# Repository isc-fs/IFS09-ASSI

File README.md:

# IFS09-ASSI

Hardware design (KiCad schematic and PCB layout) for the **Autonomous System Status Indicator (ASSI)** board of the **IFS09**, developed for the **ISC Formula Student Racing Team** (Season 2026/2027).

[-green.svg)]()

---

## Getting started

1. Create a GitHub account if you don't have one yet.
2. Download and install [GitHub Desktop](https://desktop.github.com/) (beginner) or [Git CLI](https://git-scm.com/book/en/v2/Getting-Started-Installing-Git) (advanced).

   - If this is your first time using GitHub Desktop, make sure to read the [User Manual](https://help.github.com/desktop/guides/).
   - If this is your first time using Git, start with a tutorial. There are many available online:
     - [Git Tutorial](https://git-scm.com/docs/gittutorial)
     - [Atlassian Git Tutorial](https://www.atlassian.com/git/tutorials/)
   - Keep a copy of [GitHub's Git Cheat Sheet](https://services.github.com/kit/downloads/github-git-cheat-sheet.pdf) handy as a reference.

3. Clone this repository to your machine:
   - SSH: `git@github.com:isc-fs/IFS09-ASSI.git`
   - HTTPS: `https://github.com/isc-fs/IFS09-ASSI.git`

4. To open the design, install [KiCad 10](https://www.kicad.org/download/) and set up the team library [IFS-KicadLib](https://github.com/isc-fs/IFS-KicadLib) (`ISC_KICAD_LIB` path variable), then open `hardware/ASSI/ASSI.kicad_pro`.

---

## How we work with this repository

### Main branches

The repository has two permanent branches:

**`main`** is the production branch. It contains only validated code that can be flashed onto the car. Never work directly on it.

**`dev`** is the development branch. It is the integration point where everyone's work comes together. Never work directly on it either — all changes arrive through a feature branch.

```
main  ──────────────────●──────────────────────●──▶  (validated releases only)
                        ↑                      ↑
dev   ──────●───●───●───●───●───●───●───●───●──●──▶  (continuous integration)
            ↑   ↑       ↑   ↑   ↑       ↑   ↑
          feat/1 fix/1 feat/2 fix/2   feat/3 fix/3
```

### Feature branches

All work — whether a new feature or a bug fix — is done on a **feature branch** created from `dev`. When the work is ready, a Pull Request is opened toward `dev`, reviewed, merged, and the branch is deleted.

There are two branch types, each with its own independent numeric counter:

```
feat/<n>   →  new functionality  (feat/1, feat/2, feat/3 ...)
fix/<n>    →  bug fix            (fix/1,  fix/2,  fix/3  ...)
```

The `feat` and `fix` counters are independent: `feat/2` and `fix/2` can exist at the same time with no conflict.

### Tracking branch history

Feature branches are deleted after merging to keep the repository clean. The history of each branch is preserved in **GitHub Issues**.

Every branch has one associated issue. The issue carries a **label** (`feat` or `fix`) and its title includes the branch number, for example: `[feat/3] Add CAN broadcast for mission state`. When the branch is merged and deleted, the issue is closed — becoming a permanent record of all the work done.

To see which branches are currently active: filter issues by label and status `open`.
To browse the full history: filter by label and status `closed`.
The number for the next branch of each type is the last closed issue of that type plus one.

> Example: if the last closed issue with label `feat` is `[feat/4] ...`, the next feature branch will be `feat/5`.

---

## Automation

The repository includes a GitHub Actions workflow that manages tracking issues automatically. No setup is required — it works for every developer as soon as they create a branch.

### Automatic issue creation

When a `feat/*` or `fix/*` branch is pushed to GitHub, the workflow automatically opens an issue with:

- The corresponding `[feat/N]` or `[fix/N]` title
- The correct label (`feat` or `fix`)
- A template with sections for describing the work and adding notes
- The name of the developer who created the branch

### Wrong number warning

If the branch number is not the next expected one (either too low or too high), the issue will display a warning indicating the correct number and asking the developer to delete and recreate the branch with the right name.

### Auto-fill description from first commit

When the developer makes their first commit and pushes it, the workflow automatically updates the *"What does this branch do?"* section of the issue with that commit message.

- If the developer manually edits the issue before pushing their first commit, the workflow will not overwrite the description.
- The description is only updated once — subsequent commits do not modify the issue.

---

## Step-by-step workflow

### 1. Create the branch

```bash
# Make sure you are on an up-to-date dev
git checkout dev
git pull origin dev

# Create your branch using the next available number for its type
# (last closed issue of that type + 1)
git checkout -b feat/5    # or fix/3, depending on that type's counter
```

> To find the right number: go to **Issues → filter by label `feat` or `fix` → sort by newest** and read the last number.

### 2. Push the branch

```bash
git push origin feat/5
```

The tracking issue will be opened automatically on GitHub within seconds.

### 3. Work and commit

```bash
# Make your changes and commit with a clear, descriptive message
git add .
git commit -m "short description of what this commit does"

# Push the changes
git push origin feat/5
```

The message of your **first commit** will be used to automatically fill in the issue description.

### 4. Open a Pull Request

When the work is ready, open a Pull Request on GitHub from your branch toward `dev`. In the PR description write `Closes #<issue-number>` so the issue closes automatically when the PR is merged.

Before requesting a review, check that:
- KiCad ERC and DRC report no errors
- The schematic PDF and the images in `docs/images/` match the design
- You have tested the change on the bench if applicable
- The PR targets `dev`, not `main`

### 5. Review and merge

Another team member will review the PR. Once approved, it is merged into `dev` and the branch is deleted. The issue will be closed as a permanent record.

### 6. Merging into main

When `dev` holds a set of validated changes that are ready for the car, a responsible team member opens a Pull Request from `dev` into `main`. This only happens after full firmware validation (HIL/bench).

---

## 1. Project overview

The ASSI shows the state of the Autonomous System to people around the car, as required by the Formula Student rules:

| AS state | ASSI |
| :--- | :--- |
| AS Off | Off |
| AS Ready | Yellow, continuous |
| AS Driving | Yellow, flashing |
| AS Emergency | Blue, flashing |
| AS Finished | Blue, continuous |

This board is a **passive LED board**: it has no microcontroller or logic. It lights yellow or blue depending on which of its two 24 V inputs is powered, so the colour and the flashing are decided by whatever drives those two lines.

```
            +--------------------- ASSI board ---------------------+
 IN1        |                                                      |        OUT1
 24V_YW ----+--> D2 --+--> R + G channels --> 3 rows x 5 LEDs --+  +---- 24V_YW
 24V_BL ----+--> D1 --+--> B channel -------> 3 rows x 5 LEDs --+  +---- 24V_BL
 GND -------+---------------------------------------------------+--+---- GND
            +------------------------------------------------------+
```

`IN1` and `OUT1` are wired pin to pin, so several ASSI boards can be daisy-chained from one harness branch.

### Mounting configuration

* Each ASSI is made of **two boards (A and B)** mounted next to each other, touching along the long edge, with the same orientation so the LED columns line up.
* The harness connects to `IN1` of board A, and board B connects to `OUT1` of board A (daisy chain). `OUT1` of board B is left unconnected.
* Board A carries the current of both boards: up to ~370 mA on `24V_BL` in blue mode.
* The car has three ASSIs (two sides and rear), so **6 boards** per car. A single board at the rear is being considered (5 boards per car).

---

## 2. Rules compliance (FS Rules 2026 v1.1)

| Rule | Requirement | This design |
| :--- | :--- | :--- |
| T 14.9.1 | Yellow/blue states as in the table above. "AS Driving" and "AS Emergency" flash at 2–5 Hz with 50 % duty cycle. | The board only lights the colour. The flashing frequency and duty cycle must be generated by the controller that drives `24V_YW` / `24V_BL`. |
| T 14.9.2 | Three ASSIs: one on each side behind the driver's compartment and one at the rear on the centreline. | Three ASSIs of two boards each (6 boards per car). |
| T 11.9.5 | Safe state of the ASSI signal is "AS Off". | With no supply the board is off. |
| T 11.10.1 | Black background. | The PCB solder mask is green: the enclosure must give a black background around the LEDs, or the board must be ordered with black solder mask. |
| T 11.10.1 | Minimum illuminated surface of 15 cm² with even luminous intensity. | Two boards: ≈ 40 cm² between LED centres (55.7 mm × ~72 mm). If the rear ASSI uses a single board, it has only ≈ 14.8 cm² between LED centres (≈ 20 cm² including the LED bodies), which is borderline, so that ASSI needs a diffuser or window of at least 15 cm² (see #16). |
| T 11.10.1 | LEDs without diffuser no more than 20 mm apart. | Within a board the LED pitch is 14 mm horizontally and 13 mm vertically. Between boards A and B the vertical distance is 18.7–19.2 mm, so it only stays below 20 mm if the boards touch and the LED columns are aligned. |
| T 11.10.1 | Clearly visible in very bright sunlight. | To be checked on the first boards (see #9). |

---

## 3. Schematic

<p align="center">
  
  <br>
  <sub><em>Click on the preview to open the vector PDF (<a href="Schematics-1.0.pdf">Schematics-1.0.pdf</a>)</em></sub>
</p>

### 3.1 Supply inputs

* **`24V_YW`** feeds the red and green LED channels together through diode `D2` (red + green = yellow).
* **`24V_BL`** feeds the blue LED channel through diode `D1`.
* `D1` and `D2` are Nexperia PMEG4010CEH Schottky diodes (1 A, 40 V, SOD-123F). They block reverse polarity on each input.
* `C4` (yellow rail) and `C3` (blue rail) are 100 nF 0805 capacitors to GND after each diode.

### 3.2 LED strings

* 15 × Cree **CLQ6B** RGBW LEDs (`LED1`–`LED15`), arranged as **3 rows of 5 LEDs in series**.
* Each row has its own 1206 series resistors per colour channel (`R1`–`R18`):
  * Red: 2 × 300 Ω in series (`R1`+`R2`, `R7`+`R9`, `R13`+`R15`)
  * Green: 1 × 1 kΩ (`R3`, `R10`, `R16`)
  * Blue: 3 × 47 Ω in series (`R4`+`R5`+`R6`, `R8`+`R11`+`R12`, `R14`+`R17`+`R18`)
* The white die of the CLQ6B is not used (see #17).

### 3.3 Currents and resistor power

String current: `I = (24 V − V_D − 5 × V_F) / R_string`, with V_D ≈ 0.4 V for the Schottky diode.

| Channel | V_F per LED (est.) | R_string | Current per string | Power per resistor (I²·R) |
| :--- | :---: | :---: | :---: | :---: |
| Red | 1.84 V | 600 Ω (2 × 300 Ω) | ~24 mA | ~173 mW |
| Green | 2.4 V | 1 kΩ | ~11.6 mA | ~135 mW |
| Blue | 3.0 V | 141 Ω (3 × 47 Ω) | ~61 mA | ~175 mW |

* Input current: ~183 mA on `24V_BL` (D1) and ~107 mA on `24V_YW` (D2), well below the 1 A rating of the PMEG4010CEH.
* Board dissipation: ~4.4 W in blue mode and ~2.6 W in yellow mode.
* V_F values are estimates. The currents must be confirmed on the first boards (see #6).

**Resistor rating check.** The resistors are Panasonic ERJ-P08 anti-surge thick film, 1206, **0.66 W**, ±1 %. Per the Panasonic datasheet, the rating is 100 % up to 70 °C ambient and derates linearly to 0 at 155 °C. Design rule: power ≤ 60 % of the derated rating.

| Board temperature | Derated rating | 60 % limit | Worst resistor (blue, 175 mW) |
| :---: | :---: | :---: | :---: |
| ≤ 70 °C | 0.66 W | 396 mW | 27 % of rating |
| 85 °C | 0.54 W | 326 mW | 32 % of rating |
| 100 °C | 0.43 W | 256 mW | 41 % of rating |

The 60 % rule is met for every resistor up to a board temperature of about 117 °C.

### 3.4 Connectors

`IN1` and `OUT1` are Molex Micro-Fit 3.0, 3 circuits, right-angle (43650-0300), with the same pinout:

| Pin | Net | Description |
| :---: | :--- | :--- |
| 1 | `GND` | Ground |
| 2 | `24V_YW` | 24 V supply for yellow |
| 3 | `24V_BL` | 24 V supply for blue |

The connectors overhang the board edge on purpose (see #13).

---

## 4. PCB layout

| Parameter | Value |
| :--- | :--- |
| Board size | 110 mm × 45 mm |
| Layers | 2, GND pour on both layers |
| Thickness | 1.6 mm |
| Track widths | 0.8 mm `Power` net class (`24V_YW`, `24V_BL`, `/G`, `/B`, `GND`), 0.5 mm `LED` net class (LED strings), 0.2 mm elsewhere |
| Vias | 27 × 0.6/0.3 mm, 15 of them GND stitching vias between both layers |
| Mounting holes | 4 × M3 (3.2 mm, non-plated, not connected to GND), with an 8 mm copper keep-out on both layers so the screw head and washer do not sit on copper |
| Other non-plated holes | 2 × 3.05 mm: locating pegs of the Micro-Fit connectors |
| Components | 37 SMD + 2 through-hole connectors, all on the top side |

---

## 5. Bill of materials

| Reference | Qty | Part | Manufacturer | MPN | Footprint |
| :--- | :---: | :--- | :--- | :--- | :--- |
| `LED1`–`LED15` | 15 | RGBW LED | CreeLED | CLQ6B-TKW-S1L1R1H1TBB7935BB3 | `ISC_modulos_pcb:SMT_B7935BB3_WFS` |
| `R1`, `R2`, `R7`, `R9`, `R13`, `R15` | 6 | Resistor, 300 Ω, 1 %, 0.66 W | Panasonic | ERJ-P08F3000V | `Resistor_SMD:R_1206_3216Metric_Pad1.30x1.75mm_HandSolder` |
| `R3`, `R10`, `R16` | 3 | Resistor, 1 kΩ, 1 %, 0.66 W | Panasonic | ERJ-P08F1001V | `Resistor_SMD:R_1206_3216Metric_Pad1.30x1.75mm_HandSolder` |
| `R4`–`R6`, `R8`, `R11`, `R12`, `R14`, `R17`, `R18` | 9 | Resistor, 47 Ω, 1 %, 0.66 W | Panasonic | ERJ-P08F47R0V | `Resistor_SMD:R_1206_3216Metric_Pad1.30x1.75mm_HandSolder` |
| `C3`, `C4` | 2 | Capacitor, 100 nF, 50 V, X7R | Samsung Electro-Mechanics | CL21B104KBCNNNC | `Capacitor_SMD:C_0805_2012Metric` |
| `D1`, `D2` | 2 | Schottky diode, 1 A, 40 V | Nexperia | PMEG4010CEH | `Diode_SMD:D_SOD-123F` |
| `IN1`, `OUT1` | 2 | Micro-Fit 3.0 header, 3P, right-angle | Molex | 43650-0300 | `ISC_conectores:CONN_SD-43650-001_03_MOL` |

The same list is exported as [`bom.csv`](hardware/ASSI/production/bom.csv), and the component positions as [`positions.csv`](hardware/ASSI/production/positions.csv).

---

## 6. Open points

| Issue | Status |
| :--- | :--- |
| #6 Thermal | Copper improvements done. The 30-minute bench test in blue mode is pending until boards are built. |
| #9 Yellow colour | To be checked in daylight on the first boards. |
| #10 TVS on the inputs | Low priority, not decided yet. |
| #14 3D models | To be added in IFS-KicadLib. |
| #15 Fiducials | Depends on how the board will be assembled. |
| #16 LED coverage of the board | With two boards per ASSI the illuminated surface is ≈ 40 cm². Still to be decided with the enclosure design, especially if the rear ASSI uses a single board (see T 11.10.1 above). |

---

## 7. Repository structure

```
hardware/ASSI/             KiCad project (schematic and PCB layout)
hardware/ASSI/production/  Fabrication output:
                             ASSI.zip       Gerber + drill package
                             netlist.ipc    IPC-D-356 netlist
                             bom.csv        Bill of materials with manufacturer and MPN
                             positions.csv  Component placement (pick and place)
Schematics-1.0.pdf         Schematic exported to PDF
docs/images/               Images used in this README
```

The CLQ6B symbol and footprint, the connector footprint and the ISC logo come from [IFS-KicadLib](https://github.com/isc-fs/IFS-KicadLib). The resistor, capacitor and diode footprints come from the standard KiCad libraries.

---

*ISC Racing Team — IFS09 Driverless*

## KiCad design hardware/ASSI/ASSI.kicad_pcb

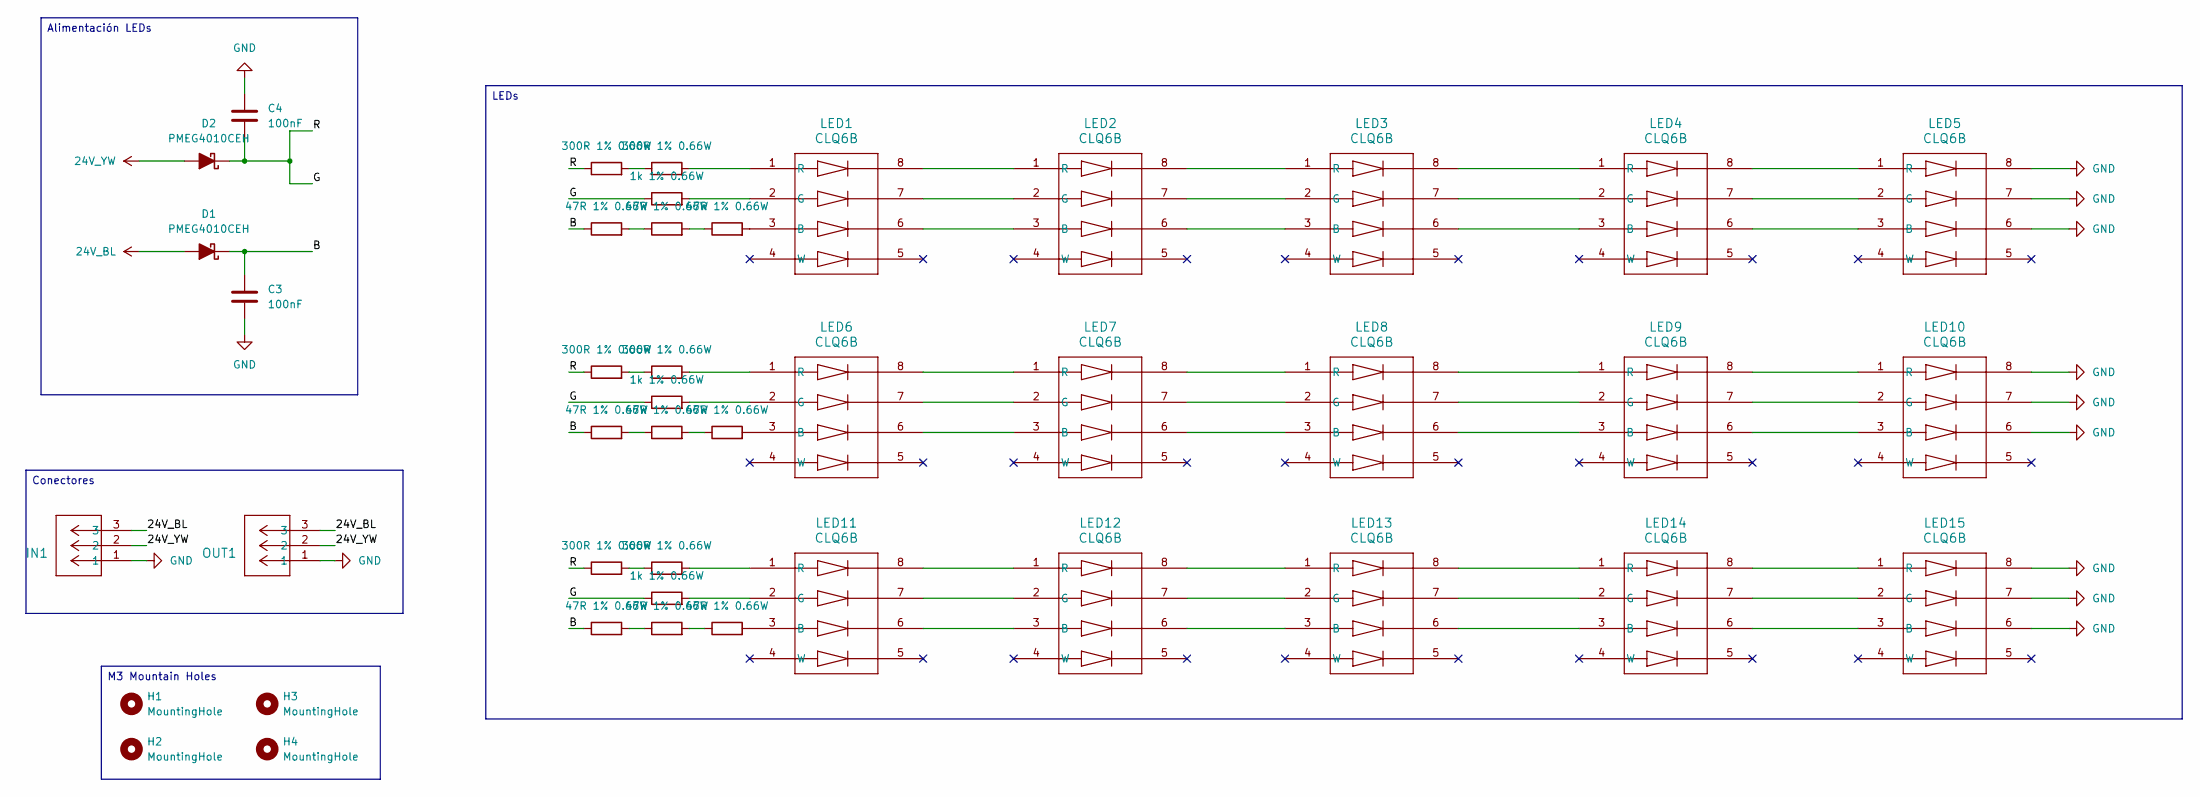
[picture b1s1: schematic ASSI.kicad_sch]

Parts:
C3, C4: 100nF; C_0805_2012Metric; MPN CL21B104KBCNNNC
D1, D2: PMEG4010CEH; D_SOD-123F; MPN PMEG4010CEH
H1, H2, H3, H4: MountingHole; MountingHole_3.2mm_M3
IN1: 436500300; CONN_SD-43650-001_03_MOL; MPN 43650-0300
LED1, LED2, LED3, LED4, LED5, LED6, LED7, LED8, LED9, LED10, LED11, LED12, LED13, LED14, LED15: CLQ6B; SMT_B7935BB3_WFS; MPN CLQ6B-TKW-S1L1R1H1TBB7935BB3
OUT1: 436500300; CONN_SD-43650-001_03_MOL; MPN 43650-0300
R1, R2, R7, R9, R13, R15: 300R 1% 0.66W; R_1206_3216Metric_Pad1.30x1.75mm_HandSolder; MPN ERJ-P08F3000V
R3, R10, R16: 1k 1% 0.66W; R_1206_3216Metric_Pad1.30x1.75mm_HandSolder; MPN ERJ-P08F1001V
R4, R5, R6, R8, R11, R12, R14, R17, R18: 47R 1% 0.66W; R_1206_3216Metric_Pad1.30x1.75mm_HandSolder; MPN ERJ-P08F47R0V

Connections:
24V_BL: D1.2 (A), IN1.3, OUT1.3
24V_YW: D2.2 (A), IN1.2, OUT1.2
/B: C3.1, D1.1 (K), R6.1, R8.1, R14.1
/G: C4.2, D2.1 (K), R2.1, R3.1, R7.1, R10.1, R13.1, R16.1
GND: C3.2, C4.1, IN1.1, LED5.6, LED5.7, LED5.8, LED10.6, LED10.7, LED10.8, LED15.6, LED15.7, LED15.8, OUT1.1
unnamed: LED1.3 (B), R4.2
unnamed: LED1.2 (G), R3.2
unnamed: LED1.1 (R), R1.2
unnamed: LED1.6, LED2.3 (B)
unnamed: LED1.7, LED2.2 (G)
unnamed: LED1.8, LED2.1 (R)
unnamed: LED2.6, LED3.3 (B)
unnamed: LED2.7, LED3.2 (G)
unnamed: LED2.8, LED3.1 (R)
unnamed: LED3.6, LED4.3 (B)
unnamed: LED3.7, LED4.2 (G)
unnamed: LED3.8, LED4.1 (R)
unnamed: LED4.6, LED5.3 (B)
unnamed: LED4.7, LED5.2 (G)
unnamed: LED4.8, LED5.1 (R)
unnamed: LED6.3 (B), R12.2
unnamed: LED6.2 (G), R10.2
unnamed: LED6.1 (R), R9.2
unnamed: LED6.6, LED7.3 (B)
unnamed: LED6.7, LED7.2 (G)
unnamed: LED6.8, LED7.1 (R)
unnamed: LED7.6, LED8.3 (B)
unnamed: LED7.7, LED8.2 (G)
unnamed: LED7.8, LED8.1 (R)
unnamed: LED8.6, LED9.3 (B)
unnamed: LED8.7, LED9.2 (G)
unnamed: LED8.8, LED9.1 (R)
unnamed: LED9.6, LED10.3 (B)
unnamed: LED9.7, LED10.2 (G)
unnamed: LED9.8, LED10.1 (R)
unnamed: LED11.3 (B), R18.2
unnamed: LED11.2 (G), R16.2
unnamed: LED11.1 (R), R15.2
unnamed: LED11.6, LED12.3 (B)
unnamed: LED11.7, LED12.2 (G)
unnamed: LED11.8, LED12.1 (R)
unnamed: LED12.6, LED13.3 (B)
unnamed: LED12.7, LED13.2 (G)
unnamed: LED12.8, LED13.1 (R)
unnamed: LED13.6, LED14.3 (B)
unnamed: LED13.7, LED14.2 (G)
unnamed: LED13.8, LED14.1 (R)
unnamed: LED14.6, LED15.3 (B)
unnamed: LED14.7, LED15.2 (G)
unnamed: LED14.8, LED15.1 (R)
unnamed: R1.1, R2.2
unnamed: R4.1, R5.2
unnamed: R5.1, R6.2
unnamed: R7.2, R9.1
unnamed: R8.2, R11.1
unnamed: R11.2, R12.1
unnamed: R13.2, R15.1
unnamed: R14.2, R17.1
unnamed: R17.2, R18.1

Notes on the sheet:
Conectores
M3 Mountain Holes
LEDs
Alimentación LEDs

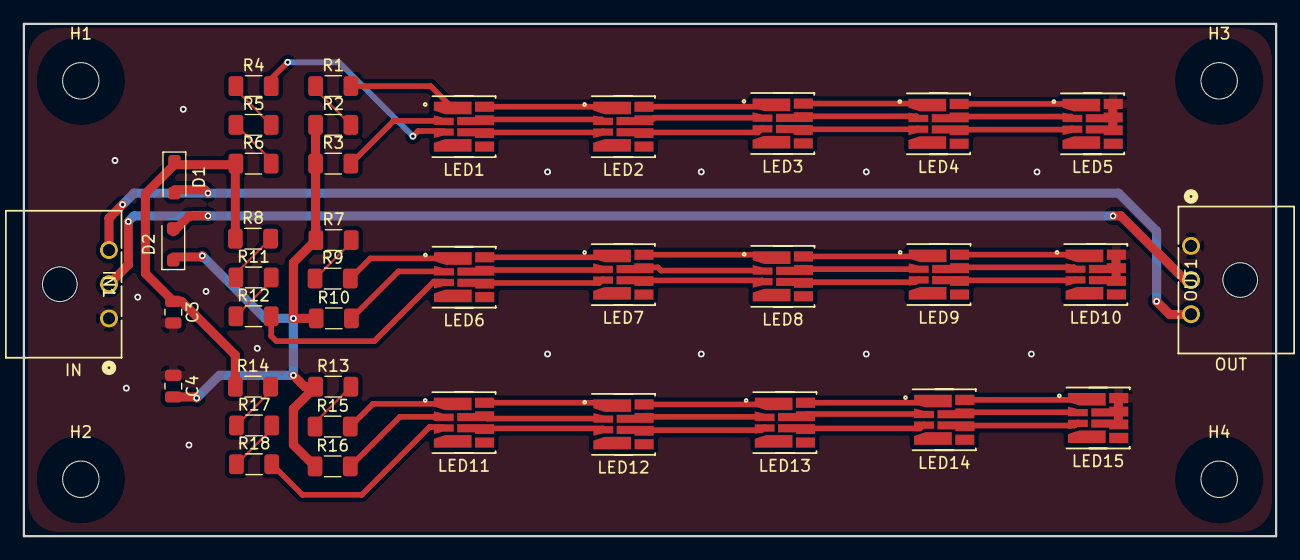
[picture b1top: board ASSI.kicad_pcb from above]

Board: 2 copper layers, 110.0 x 45.0 mm, 44 parts (1 on the bottom side), 59 nets.

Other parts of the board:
G3: LOGO; LogoISC

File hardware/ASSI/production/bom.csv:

"Reference","Value","Footprint","Manufacturer","MPN","Qty"
"C3,C4","100nF","Capacitor_SMD:C_0805_2012Metric","Samsung Electro-Mechanics","CL21B104KBCNNNC","2"
"D1,D2","PMEG4010CEH","Diode_SMD:D_SOD-123F","Nexperia","PMEG4010CEH","2"
"IN1,OUT1","436500300","ISC_conectores:CONN_SD-43650-001_03_MOL","Molex","43650-0300","2"
"LED1-LED15","CLQ6B","ISC_modulos_pcb:SMT_B7935BB3_WFS","CreeLED","CLQ6B-TKW-S1L1R1H1TBB7935BB3","15"
"R1,R2,R7,R9,R13,R15","300R 1% 0.66W","Resistor_SMD:R_1206_3216Metric_Pad1.30x1.75mm_HandSolder","Panasonic","ERJ-P08F3000V","6"
"R3,R10,R16","1k 1% 0.66W","Resistor_SMD:R_1206_3216Metric_Pad1.30x1.75mm_HandSolder","Panasonic","ERJ-P08F1001V","3"
"R4-R6,R8,R11,R12,R14,R17,R18","47R 1% 0.66W","Resistor_SMD:R_1206_3216Metric_Pad1.30x1.75mm_HandSolder","Panasonic","ERJ-P08F47R0V","9"
